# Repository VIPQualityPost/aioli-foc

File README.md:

# AIOLI-FOC (All In One Low I - FOC)

Small, low current (I) closed loop simpleFOC driver board, that can be assembled for &lt;$10 with mostly basic components at LCSC. Has USB C for power, serial communication (USB CDC), and DFU firmware updates. The CANBUS peripheral is exposed on both edges for "stitching" boards together using the Kyocera B2B connector used on the STLINK-V3-MINIE. SWD + UART via STLINK 14 pin connector.

The target for this project was to create an all-in-one simpleFOC board with high resolution magnetic encoder, better MCU than the previous STM32F103, CANBUS for multi board communication, and be assembled with top-side only components. The board is 4 layers (which at this size, does not add any cost over the 2-layers). Additionally, it has a compact size of 40x40mm.

# Building

- Install [platformio core](https://docs.platformio.org/en/latest/core/installation/methods/index.html)
- Run `pio run --environment aioli-foc`

Alternately you can use the vscode integration

# Flashing

There are two options for flashing - DFU mode, and with stlink hardware

## DFU Mode

DFU mode can be done via the USB port, but due to the st32's default settings, pin PB8 will conflict with the CAN XCVR line, causing the st32 to boot to DFU mode every reset, losing the firmware and requiring recompilation. This is fine for testing but you'll need to use stlink to change that setting, and to program the st32 without being in DFU mode.

To program in DFU mode, set `upload_protocol` to `dfu` in `platformio.ini`.

You can then use `pio run --target upload --environment aioli-foc` or press `Upload` in vscode.

Note that `Upload and Monitor` may not work because `dfu-util` tends to think the upload failed even if it didn't.

## stlink Mode
- Acquire an [stlink v3 minie](https://www.st.com/en/development-tools/stlink-v3minie.html) or equvalent
- Connect the stlink to the 1.27mm 2x7 header on the board labeled `stm32g431`. This will require either soldering a header in (it is not in the JLBPCB BOM), or just jamming it in and holding it long enough to make contact.
- Once per board you will have to use `STM32CubeProgrammer` or `STM32 ST-LINK Utility` to set the Option Byte under User Configuration named `nSWBOOT0` to unchecked. This will prevent the st32 from going into DFU mode on every reset.
- Make sure to set `upload_protocol` back to `stlink` in `platformio.ini`
- Run `pio run --target upload --target monitor --environment aioli-foc` or click `Upload and Monitor` in vscode

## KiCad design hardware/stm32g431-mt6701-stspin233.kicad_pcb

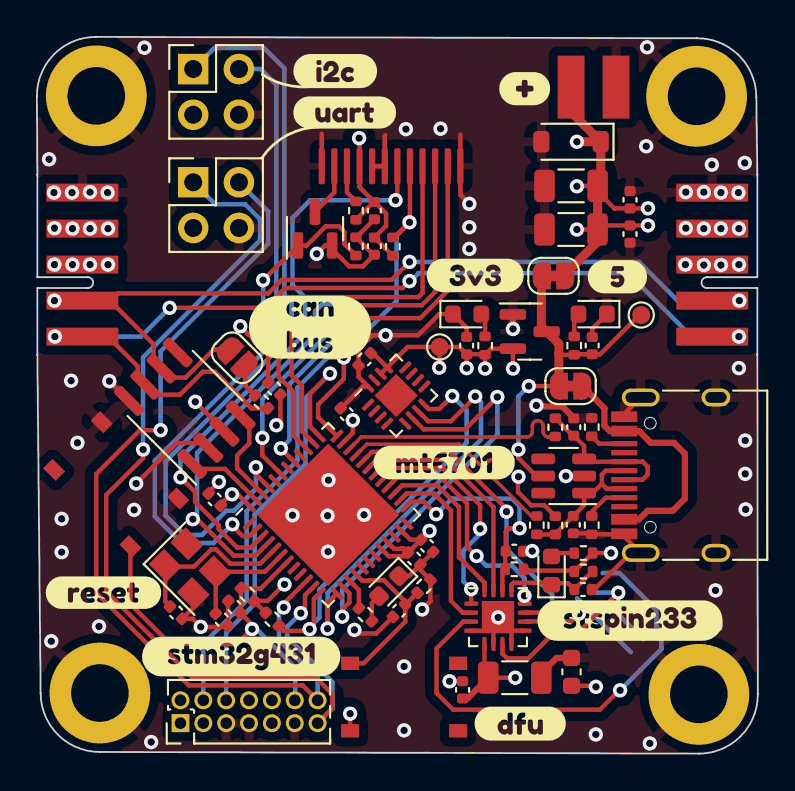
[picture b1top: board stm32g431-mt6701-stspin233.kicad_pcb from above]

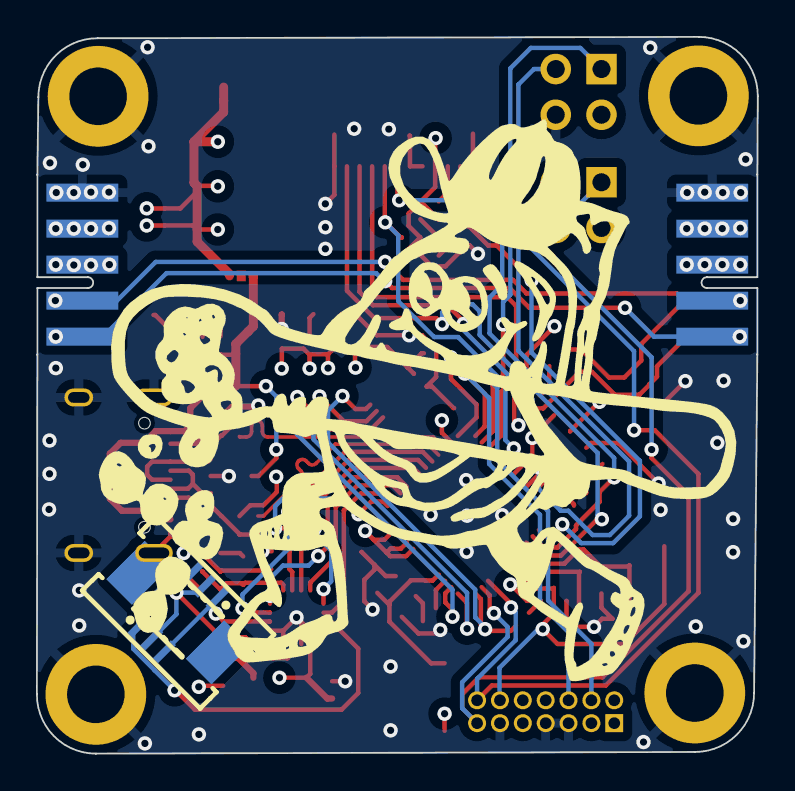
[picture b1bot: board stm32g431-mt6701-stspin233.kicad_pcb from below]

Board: 4 copper layers, 40.1 x 39.8 mm, 89 parts (5 on the bottom side), 53 nets.

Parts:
C101, C201, C202, C203, C204, C207, C208, C401, C501, C502: 0.1u; C_0402_1005Metric
C205, C206: 20p; C_0402_1005Metric
C301: 1n; C_0402_1005Metric
C302: 10n; C_0402_1005Metric
C303: 22u; C_0603_1608Metric
C304: 2.2u; C_0402_1005Metric
C601, C602: 47p; C_0402_1005Metric
C701, C703, C704: 100u; C_1206_3216Metric
C702, C706: 1u; C_0402_1005Metric
C705, C707: 10u; C_0402_1005Metric
D101: B5819W; D_SOD-123
D201: USER; D_0603_1608Metric
D301: FAULT; D_0603_1608Metric
D701: 5V; D_0603_1608Metric
D702: 3V3; D_0603_1608Metric
H101, H102, H103, H104: M3; MountingHole_3.2mm_M3_DIN965_Pad
J101: I2C; PinHeader_2x02_P2.54mm_Vertical
J102: UART; PinHeader_2x02_P2.54mm_Vertical
J103: CANBUS_IN; AVX-009159010061911
J104: CANBUS_OUT; AVX-009159010061911
J106: CAN TERMINATION; SolderJumper-2_P1.3mm_Open_RoundedPad1.0x1.5mm
J107: EXT_PWR; JST-XH-edgemount-2p
J109: MOT_FPC; FPC-SMD_3P-P1.00_HDGC_1.0K-LS-3PWB-BOTTOMCONTACT
J110: MOT_FPC2; FPC-SMD_3P-P1.00_HDGC_1.0K-LS-3PWB-BOTTOMCONTACT
J201: STDC14; PinHeader_2x07_P1.27mm_Vertical
J601: USB_C_Receptacle_USB2.0; USB_C_Receptacle_HRO_TYPE-C-31-M-12
JP601: USB5V; SolderJumper-2_P1.3mm_Bridged_RoundedPad1.0x1.5mm
JP701: EXT5V; SolderJumper-2_P1.3mm_Bridged_RoundedPad1.0x1.5mm
Q501: AO3400A; SOT-23
R101: 120R; R_0402_1005Metric
R201, R204, R205, R701: 5.1k; R_0402_1005Metric
R202, R203, R401, R501, R503: 10k; R_0402_1005Metric
R206, R207, R502: 22R; R_0402_1005Metric
R301, R302: 18k; R_0402_1005Metric
R303, R702: 3.3k; R_0402_1005Metric
R601: 1.5k; R_0402_1005Metric
SW201: DFU; TS-1187A-B-A-B
SW202: RESET; TS-1187A-B-A-B
TP701: 5V; TestPoint_Pad_D1.0mm
TP702: 3V3; TestPoint_Pad_D1.0mm
U101: SN65HVD230; SOIC-8_3.9x4.9mm_P1.27mm
U201: STM32G431; QFN-48-1EP_7x7mm_P0.5mm_EP5.6x5.6mm
U301: STSPIN233; VQFN-16-1EP_3x3mm_P0.5mm_EP1.8x1.8mm
U401: MT6701; QFN-16-1EP_3x3mm_P0.5mm_EP1.7x1.7mm
U501: GC9A01; GC9A01Round1.28_flipped_mount_easy_esc
U601: SRV05-4; SOT-23-6
U701: XC6206; SOT-23
Y201: 12MHz; Crystal_SMD_3225-4Pin_3.2x2.5mm
kibuzzard-649CD3B4: G***; kibuzzard-649CD3B4
kibuzzard-649CD3ED: G***; kibuzzard-649CD3ED
kibuzzard-649CD42A: G***; kibuzzard-649CD42A
kibuzzard-649CD53A: G***; kibuzzard-649CD53A
kibuzzard-649CD397: G***; kibuzzard-649CD397
kibuzzard-649CD402: G***; kibuzzard-649CD402
kibuzzard-649CD439: G***; kibuzzard-649CD439
kibuzzard-649CD577: G***; kibuzzard-649CD577
kibuzzard-649D001F: G***; kibuzzard-649D001F
kibuzzard-649D0025: G***; kibuzzard-649D0025
kibuzzard-649DBE26: G***; kibuzzard-649DBE26
kibuzzard-649DBEEB: G***; kibuzzard-649DBEEB

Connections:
+3V3: C101.1, C201.1, C202.1, C203.1, C204.1, C401.1, C501.1, C502.1, C706.1, J201.3 (VCC), R203.1, R301.1, R302.1, R303.2, R401.1, R501.1, R502.1, R601.1, R702.1, SW201.2, TP702.1, U101.3 (VCC), U201.20 (VREF+), U201.21 (VDDA), U201.23 (VDD), U201.35 (VDD), U201.48 (VDD), U401.13 (VDD), U401.14 (MODE), U501.4 (VDD), U701.2 (VOUT)
+5V: C702.1, JP601.2 (B), JP701.2 (B), R701.1, TP701.1, U601.5 (VP), U701.3 (VIN)
/CAN_H: J103.1, J103.6, J104.1, J104.6, R101.2, U101.7 (CANH)
/CAN_L: J103.2, J103.7, J104.2, J104.7, J106.1, U101.6 (CANL)
/I2C_SCL: J101.1, U201.38 (PA15)
/I2C_SDA: J101.2, U201.45 (PB7)
/UART_RX: J102.2, J201.14 (VCP_TX), U201.10 (PA2)
/UART_TX: J102.1, J201.13 (VCP_RX), U201.11 (PA3)
/display/BL_A: R502.2, U501.3 (LEDA)
/display/BL_K: Q501.3 (D), U501.2 (LEDK)
/display/TFT_BL: Q501.1 (G), R503.1, U201.2 (PC13)
/display/TFT_COPI: U201.43 (PB5), U501.10 (MOSI)
/display/TFT_DC: U201.3 (PC14), U501.7 (DC)
/display/TFT_RESET: U201.4 (PC15), U501.11 (nRESET)
/display/TFT_SCK: U201.39 (PC10), U501.9 (SCK)
/display/~TFT_CS: R501.2, U201.41 (PB3), U501.8 (nCS)
/encoder/ENC_CIPO: U201.14 (PA6), U401.6 (A/SDA/DO)
/encoder/ENC_SCK: U201.13 (PA5), U401.7 (B/SCL/CLK)
/encoder/~ENC_CS: R401.2, U201.12 (PA4), U401.8 (Z/~CSN)
/mcu/DFU: C207.1, R202.1, SW201.1, U201.16 (PC4)
/mcu/FDCAN1_RX: U101.4 (R), U201.46 (PB8)
/mcu/FDCAN1_TX: U101.1 (D), U201.47 (PB9)
/mcu/RESET: C208.1, J201.12 (~RST), R203.2, SW202.1, U201.7 (PG10)
/mcu/SDIO: J201.4 (JTMS/SWDIO), U201.36 (PA13)
/mcu/SWCLK: J201.6 (JCLK/SWCLK), U201.37 (PA14)
/mcu/TIM1_CH1: U201.30 (PA8), U301.1 (INU)
/mcu/TIM1_CH1N: U201.26 (PB13), U301.2 (ENU)
/mcu/TIM1_CH2: U201.31 (PA9), U301.15 (INV)
/mcu/TIM1_CH2N: U201.27 (PB14), U301.16 (ENV)
/mcu/TIM1_CH3: U201.32 (PA10), U301.11 (INW)
/mcu/TIM1_CH3N: U201.28 (PB15), U301.12 (ENW)
/mcu/UCPD1_CC1: J601.A5 (CC1), R205.2
/mcu/UCPD1_CC2: J601.B5 (CC2), R204.1
/mcu/USBD_M: R206.1, U201.33 (PA11)
/mcu/USBD_P: R207.2, U201.34 (PA12)
/mcu/USB_M: C601.1, J601.A7 (D-), J601.B7 (D-), R206.2, R601.2, U601.1 (IO1)
/mcu/USB_P: C602.1, J601.A6 (D+), J601.B6 (D+), R207.1, U601.3 (IO2)
/mcu/XIN: C206.1, U201.6 (PF1), Y201.3
/mcu/XOUT: C205.1, U201.5 (PF0), Y201.1
/mcu/~MOT_SHDN: C301.1, R301.2, U201.25 (PB12), U301.14 (STBY/RESET)
/motor driver/EN/FAULT: C302.1, D301.1 (K), R302.2, U301.13 (EN/FAULT)
/motor driver/MOT_U: J109.1, J110.3, U301.3 (OUTU)
/motor driver/MOT_V: J109.2, J110.2, U301.7 (OUTV)
/motor driver/MOT_W: J109.3, J110.1, U301.10 (OUTW)
/usb/USB_5V: J601.A4 (VBUS), J601.A9 (VBUS), J601.B4 (VBUS), J601.B9 (VBUS), JP601.1 (A)
GND: C101.2, C201.2, C202.2, C203.2, C204.2, C205.2, C206.2, C207.2, C208.2, C301.2, C302.2, C303.2, C304.2, C401.2, C501.2, C502.2, C601.2, C602.2, C701.2, C702.2, C703.2, C704.2, C705.2, C706.2, C707.2, D101.2 (A), D201.1 (K), D701.1 (K), D702.1 (K), H101.1, H102.1, H103.1, H104.1, J101.4, J102.4, J103.5, J103.10, J104.5, J104.10, J107.2, J201.5 (GND), J201.7 (GND), J201.11 (GNDDetect), J601.A1 (GND), J601.A12 (GND), J601.B1 (GND), J601.B12 (GND), J601.S1 (SHIELD), Q501.2 (S), R202.2, R204.2, R205.1, R503.2, SW202.2, U101.2 (GND), U101.8 (Rs), U201.49 (VSS), U301.4 (SENSEU), U301.6 (GND), U301.8 (SENSEV), U301.9 (SENSEW), U301.17 (GND), U401.16 (GND), U501.1 (GND), U501.5 (GND), U501.6 (GND), U501.12 (GND), U601.2 (VN), U701.1 (GND), Y201.2, Y201.4
unnamed: D201.2 (A), R201.2
unnamed: D301.2 (A), R303.1
unnamed: D701.2 (A), R701.2
unnamed: D702.2 (A), R702.2
unnamed: J106.2, R101.1
unnamed: R201.1, U201.15 (PA7)
Vmot: C303.1, C304.1, C701.1, C703.1, C704.1, C705.1, C707.1, D101.1 (K), J101.3, J102.3, J103.3, J103.4, J103.8, J103.9, J104.3, J104.4, J104.8, J104.9, J107.1, JP701.1 (A), U301.5 (VS)

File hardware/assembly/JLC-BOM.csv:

Comment,Designator,Footprint,JLCPCB Part #
USB_C_Receptacle_USB2.0,J601,HRO_TYPE-C-31-M-12,C165948
10u,"C707,C705",0402_C,
SN65HVD230,U101,SOIC-8,C12084
22R,"R206,R207,R502",0402_R,
3.3k,"R303,R702",0402_R,
0.1u,"C502,C501,C202,C204,C101,C401,C203,C201,C207,C208",0402_C,
18k,"R301,R302",0402_R,
AO3400A,Q501,SOT-23,C20917
10k,"R203,R401,R501,R202,R503",0402_R,
22u,C303,0602_C,
10n,C302,0402_C,
1u,"C706,C702",0402_C,
LED,"D301,D201,D701,D702",0603_D,C2290
100u,"C701,C704,C703",1206_C,
20p,"C205,C206",0402_C,
B5819W,D101,D_SOD-123,C8598
12MHz,Y201,Crystal_3225,C9002
SRV05-4,U601,SOT-23-6,C85364
STSPIN233,U301,VQFN-16,C2653468
5.1k,"R204,R701,R201,R205",0402_R,
XC6206,U701,SOT-23,C5446
47p,"C602,C601",0402_C,
STM32G431,U201,QFN-48,C529356
2.2u,C304,0402_C,
120R,R101,0402_R,
BUTTON,"SW201,SW202",TS-1187A-B-A-B,C318884
1n,C301,0402_C,
MT6701,U401,QFN-16,C2913974

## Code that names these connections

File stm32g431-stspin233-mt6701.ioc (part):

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Mcu.Name=STM32G431C(6-8-B)Ux
Mcu.Package=UFQFPN48
Mcu.UserName=STM32G431CBUx
PA10.Signal=S_TIM1_CH3
PA11.Mode=Device
PA11.Signal=USB_DM
PA12.Mode=Device
PA12.Signal=USB_DP
PA13.Mode=Serial_Wire
PA13.Signal=SYS_JTMS-SWDIO
PA14.Mode=Serial_Wire
PA14.Signal=SYS_JTCK-SWCLK
PA15.Mode=I2C
PA15.Signal=I2C1_SCL
PA2.Mode=Asynchronous
PA2.Signal=USART2_TX
PA3.Mode=Asynchronous
PA3.Signal=USART2_RX
PA5.Mode=RX_Only_Simplex_Unidirect_Master
PA5.Signal=SPI1_SCK
PA6.Mode=RX_Only_Simplex_Unidirect_Master
PA6.Signal=SPI1_MISO
PA8.Signal=S_TIM1_CH1
PA9.Signal=S_TIM1_CH2
PB13.Mode=PWM Generation1 CH1 CH1N
PB13.Signal=TIM1_CH1N
PB14.Mode=PWM Generation2 CH2 CH2N
PB14.Signal=TIM1_CH2N
PB15.Mode=PWM Generation3 CH3 CH3N
PB15.Signal=TIM1_CH3N
PB3.GPIOParameters=GPIO_Label
PB3.GPIO_Label=SPI3_CS
PB3.Signal=GPIO_Output
PB4.Mode=Sink_AllSignals
PB4.Signal=UCPD1_CC2
PB5.Mode=Full_Duplex_Master
PB5.Signal=SPI3_MOSI
PB6.Mode=Sink_AllSignals
PB6.Signal=UCPD1_CC1
PB7.Mode=I2C
PB7.Signal=I2C1_SDA
PB8-BOOT0.Mode=FDCAN_Activate
PB8-BOOT0.Signal=FDCAN1_RX
PB9.Mode=FDCAN_Activate
PB9.Signal=FDCAN1_TX
PC10.Mode=Full_Duplex_Master
PC10.Signal=SPI3_SCK
PC11.Mode=Full_Duplex_Master
PC11.Signal=SPI3_MISO
PC13.Mode=PWM Generation4 CH4N
PC13.Signal=TIM8_CH4N
PC14-OSC32_IN.GPIOParameters=GPIO_Label
PC14-OSC32_IN.GPIO_Label=TFT_DC
PC14-OSC32_IN.Signal=GPIO_Output
PC15-OSC32_OUT.GPIOParameters=GPIO_Label
PC15-OSC32_OUT.GPIO_Label=TFT_RESET
PC15-OSC32_OUT.Signal=GPIO_Output
PF0-OSC_IN.Mode=HSE-External-Oscillator
PF0-OSC_IN.Signal=RCC_OSC_IN
PF1-OSC_OUT.Mode=HSE-External-Oscillator
PF1-OSC_OUT.Signal=RCC_OSC_OUT
RCC.HSE_VALUE=12000000
RCC.SYSCLKFreq_VALUE=16000000
board=custom

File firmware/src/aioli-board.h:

#pragma once

// MOTOR DRIVER
#define U_PWM       PA8
#define U_EN        PB13
#define V_PWM       PA9
#define V_EN        PB14
#define W_PWM       PA10
#define W_EN        PB15

// MOTOR ENCODER (SPI1)
#define ENC_CIPO    PA6
#define ENC_SCK     PA5
#define ENC_CS      PA4

// CANBUS
#define CAN_TX      PB9
#define CAN_RX      PB8

// GC9AO1 TFT DISPLAY (SPI3)
#define TFT_COPI    PB5    
#define TFT_SCK     PC10
#define TFT_CS      PB3
#define TFT_DC      PC14
#define TFT_BL      PC13 // PWM TIM8CH4N

// GENERAL SPI (SPI3)
#define SPI3_CS     PB11 

// GENERAL UART
#define UART2_TX    PA2
#define UART2_RX    PA3

// GENERAL I2C
#define I2C1_SDA    PB7
#define I2C1_SCL    PA15

//MISC
#define USER_LED    PA7
#define DFU_PIN     PC4

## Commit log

2023-06-22 work on layout
2023-06-29 finalize fab files
2023-06-29 fix gitignore
2023-06-30 start working on firmware
2023-06-30 update schematic
2023-06-30 Move platform.io to root and include README
2023-06-30 fix board dir
2023-07-01 start on adding CANBUS
2023-07-01 start on DFU implementation
2023-07-02 Get basic CAN implemented
2023-07-02 clean up some files
2023-07-02 remove .vscode folder
2023-07-03 update schematic (Vref+ tie to Vdd) and go through ERC check
2023-07-07 Update with real photos
2023-07-08 Fix swapped USB pins
2023-07-08 Base firmware working
2023-07-11 update schematic to remove debounce cap
2023-07-11 Change DFU_BUTTON to USER_BUTTON
2023-07-11 Add Adafruit gfx libraries for TFT
2023-07-11 Fix submodule problem
2023-07-11 Add SimpleCanLib submodule
2023-07-11 Fix the SimpleCanLib submodule
2023-07-11 remove old simplecan
2023-07-12 Get barebones HAL CAN working
2023-07-12 Add cpl, bom, fix soldermask on edge conn
2023-07-13 Add CAN application profile
2023-07-14 more work on canbus
2023-07-14 Add mechanical files
2023-07-15 Add assembly files
2023-08-21 get canbus working
2023-08-21 canbus interrupts working
2023-08-23 get USB detection working
2023-08-23 update gitignore
2023-08-26 prototype unique can ID search
2023-08-26 prototype canbus unique id search
2024-05-22 Fix up imports, fix typo in BOM, start readme
2024-05-23 Add pre-commit and linters/formatters
2024-05-23 Add a bunch of linting
2024-05-23 Exclude step files from trailing whitespace
2024-05-23 Nuke accidentally added file
2024-05-23 Add a clang-format file
2024-05-26 Add a 3 screw generic motor mount, add to README
2024-05-26 Update README to fix images
2024-05-29 New parametric design.
2025-10-15 fix build errors
